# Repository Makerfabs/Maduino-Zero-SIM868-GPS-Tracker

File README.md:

# Maduino-Zero-SIM868-GPS-Tracker
Maduino Zero SIM868 GPS Tracker

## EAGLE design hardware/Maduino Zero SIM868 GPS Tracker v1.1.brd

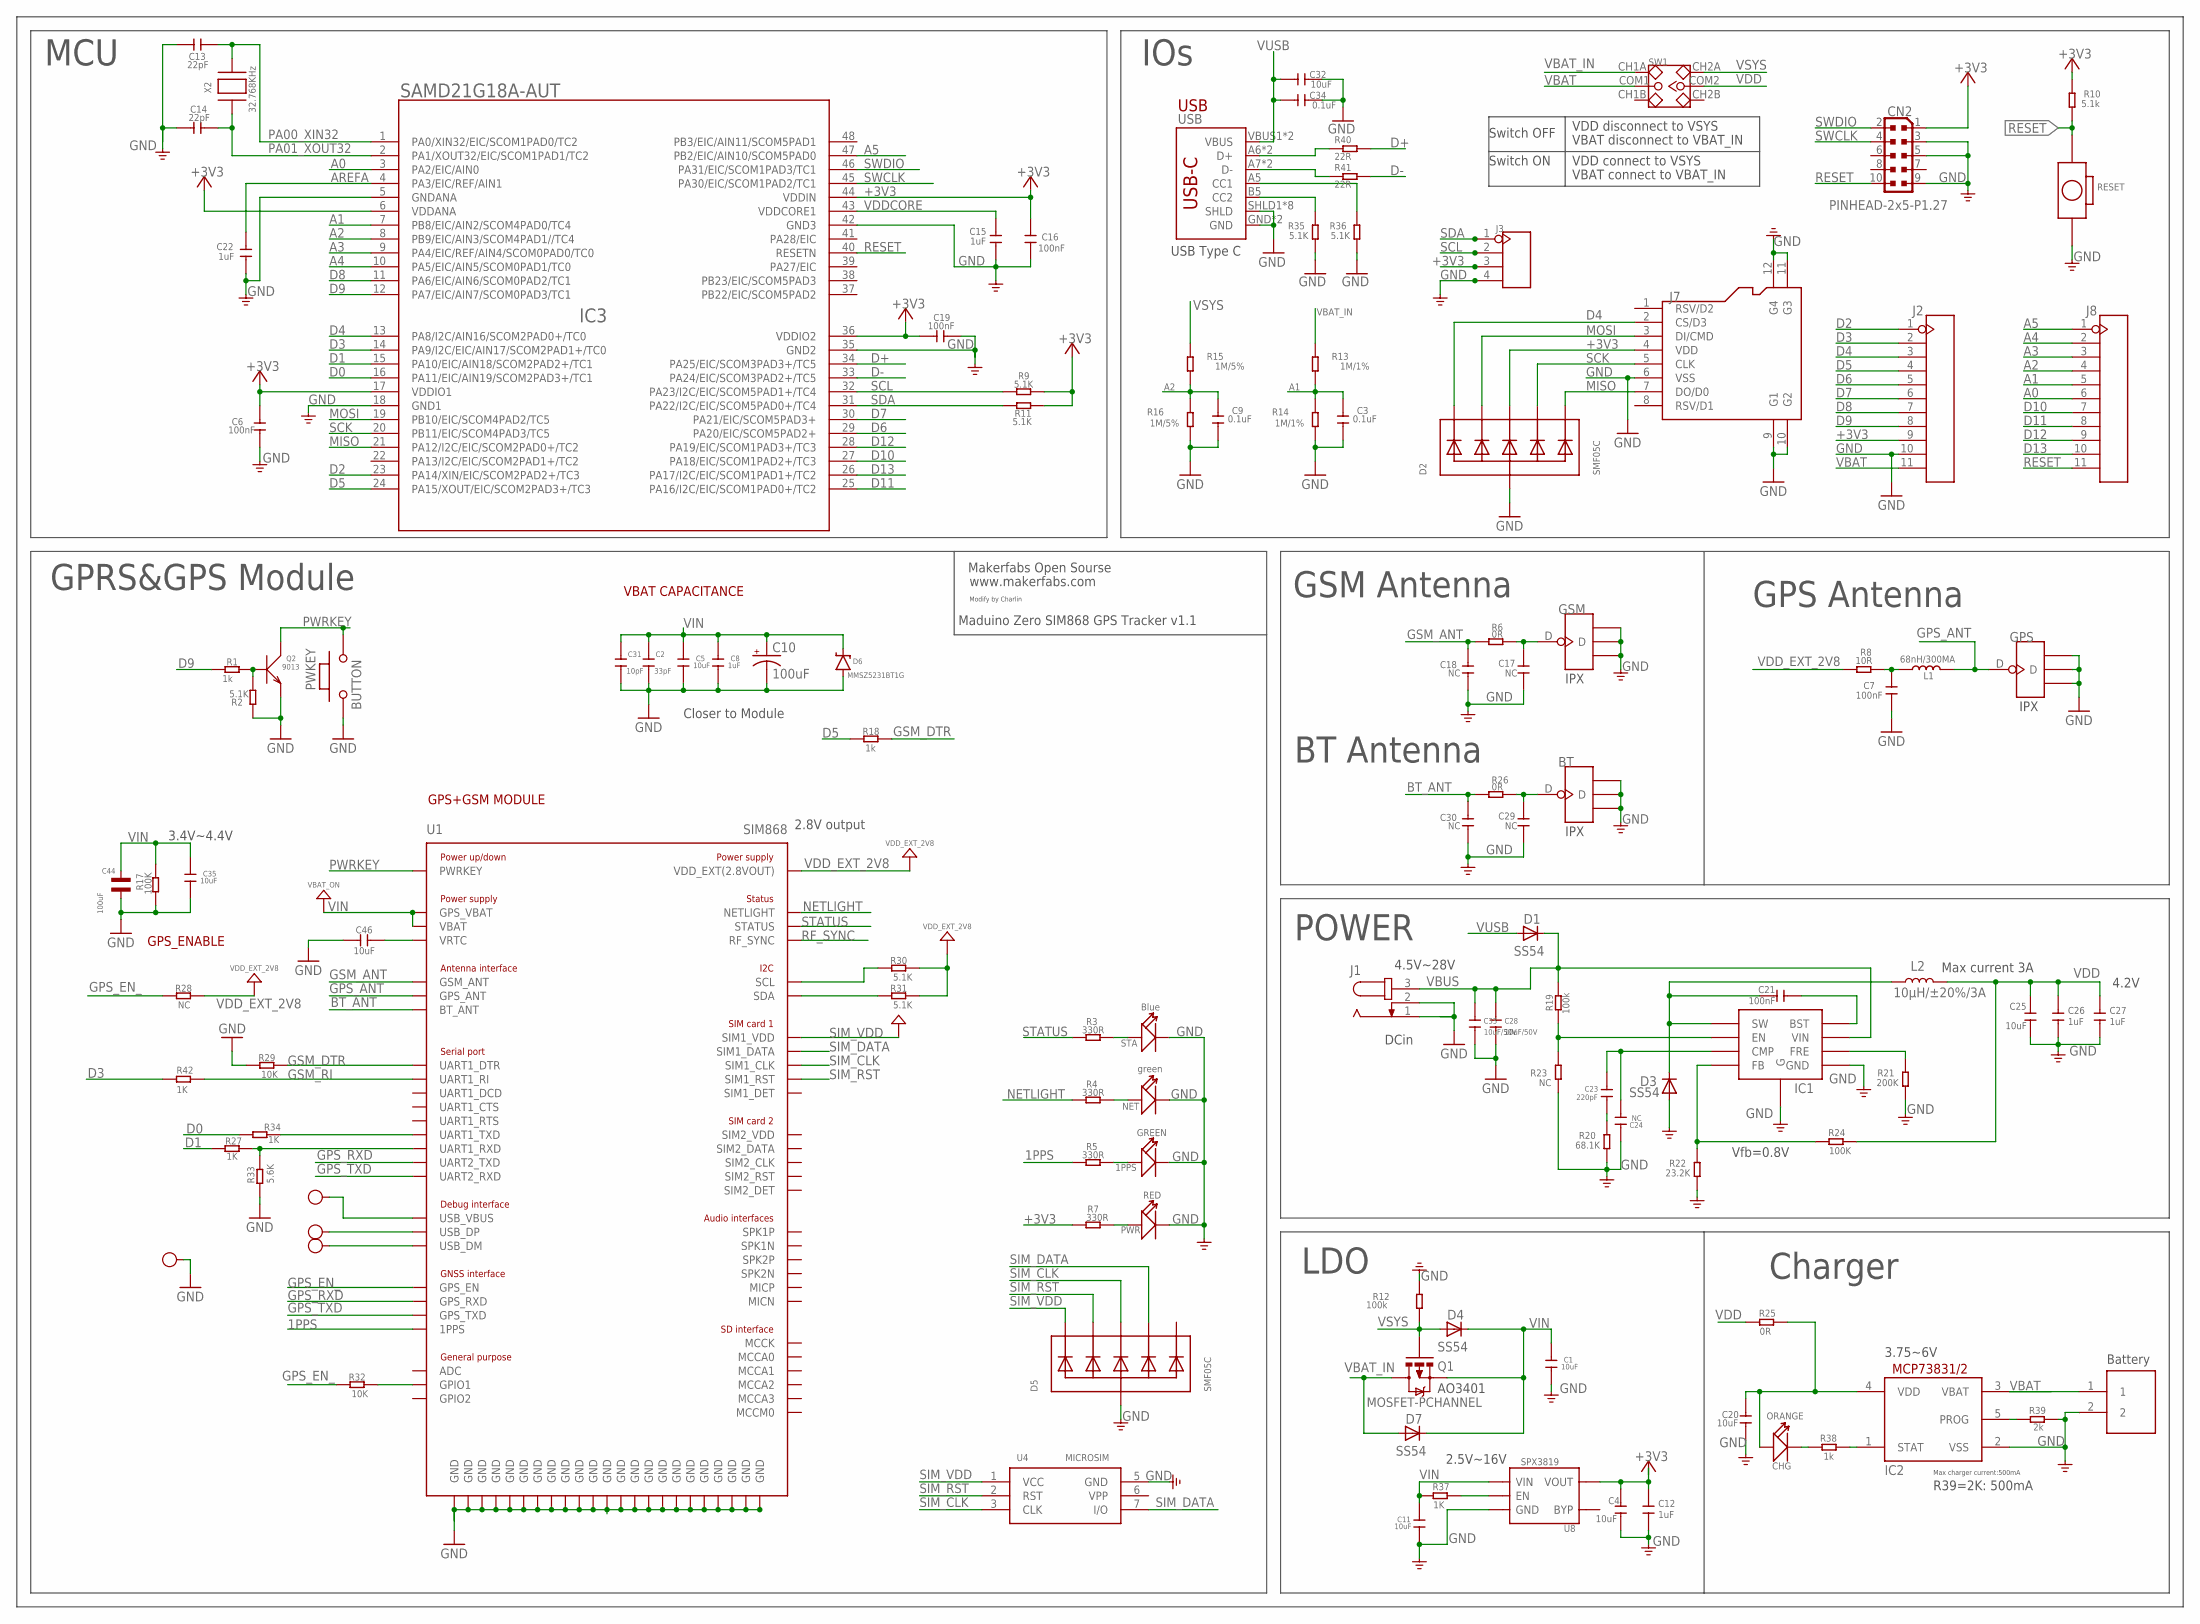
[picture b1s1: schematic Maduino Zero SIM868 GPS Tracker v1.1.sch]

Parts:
1PPS: GREEN; LED-0603
BT: ANTENNA-U-FL; 4P-U-FL
C1, C4, C5, C11, C20, C25, C32, C35: 10uF; 0603
C2: 33pF; 0603
C3, C9, C34: 0.1uF; 0603
C6, C7, C16, C19, C21: 100nF; 0603
C8, C12, C15, C22, C26, C27: 1uF; 0603
C10: 100uF; EIA3528
C13, C14: 22pF; 0603
C17, C18, C29, C30: NC; 0402
C23: 220pF; 0603
C24: NC; 0603
C28, C33: 10uF/50V; 0603
C31: 10pF; 0603
C44: 100uF; C1206; MPN CL31A107MQHNNNE
C46: 10uF; 0805
CHG: ORANGE; D0603
CN2: PINHEAD-2x5-P1.27; PINHEAD_2X05_127
D1, D3, D4, D7: SS54; DO-214AC
D2, D5: SMF05C; SOT363
D6: MMSZ5231BT1G; SOD-123
DN: TEST-POINT'4545'; TP-D45MIL; PARTNO DNP
DP: TEST-POINT'4545'; TP-D45MIL; PARTNO DNP
GND20: TEST-POINT'4545'; TP-D45MIL; PARTNO DNP
GPS: ANTENNA-U-FL; 4P-U-FL
GSM: ANTENNA-U-FL; 4P-U-FL
IC1: MP1584; SOIC8E
IC2: MCP73831/OT; SOT23-5L
IC3: SAMD21G18A-AUT; TQFP48-7X7
J1: JACK-PLUG1; SPC4078
J2, J8: HEADER-11P-2.54; 11P-2.54
J3: HEADER-4P-60/35MILROUND; 4P-65/35ROUND
J6: PH2.0-2P-90-DIP
J7: HOLDER-MICROSD-8P; 8P-SMD
L1: 68nH/300MA; L0603
L2: 10µH/±20%/3A; SRN6045
NET: green; LED-0603
PWKEY: BUTTON; 157SW
PWR: RED; LED-0603
Q1: MOSFET-PCHANNEL; SOT23-3
Q2: 9013; SOT23
R1, R18, R38: 1k; R0603
R2, R9, R11, R30, R31, R35, R36: 5.1K; R0603
R3, R4, R5, R7: 330R; R0603
R6, R25, R26: 0R; R0603
R8: 10R; R0603
R10: 5.1k; R0603
R12, R19: 100k; R0603
R13, R14: 1M/1%; R0603
R15, R16: 1M/5%; R0603
R17, R24: 100K; R0603
R20: 68.1K; R0603
R21: 200K; R0603
R22: 23.2K; R0603
R23, R28: NC; R0603
R27, R34, R37, R42: 1K; R0603
R29, R32: 10K; R0603
R33: 5.6K; R0603
R39: 2k; R0603
R40, R41: 22R; R0603
RESET: BOTTON-2P-90D; 2P-7.62X3.56-90D
STA: Blue; LED-0603
SW1: SWITCH-2CH-6P; 6P-2CH-2.54-7.6X3.0
U1: SIM868; MPN SIM868
U4: MICROSIM
U8: SPX3819; SOT23-5
USB: USB_C5; USB-C-16P-5
VUSB: TEST-POINT'4545'; TP-D45MIL; PARTNO DNP
X2: 32.768KHz; XTAL3215

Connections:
1PPS: R5.1, U1.60_ (1PPS)
+3V3: C4.2, C6.2, C12.2, C16.1, C19.1, CN2.1, D2.4 (C3), IC3.6 (VDDANA), IC3.17 (VDDIO1), IC3.36 (VDDIO2), IC3.44 (VDDIN), J2.9, J3.3, J7.4 (VDD), R7.1, R9.2, R10.2, R11.2, U8.5 (VOUT)
A0: IC3.3 (PA2/EIC/AIN0), J8.6
A1: C3.1, IC3.7 (PB8/EIC/AIN2/SCOM4PAD0/TC4), J8.5, R13.1, R14.2
A2: C9.1, IC3.8 (PB9/EIC/AIN3/SCOM4PAD1//TC4), J8.4, R15.1, R16.2
A3: IC3.9 (PA4/EIC/REF/AIN4/SCOM0PAD0/TC0), J8.3
A4: IC3.10 (PA5/EIC/AIN5/SCOM0PAD1/TC0), J8.2
A5: IC3.47 (PB2/EIC/AIN10/SCOM5PAD0), J8.1
AREFA: C22.1, IC3.4 (PA3/EIC/REF/AIN1)
BT_ANT: C30.2, R26.1, U1.20_ (BT_ANT)
D0: IC3.16 (PA11/EIC/AIN19/SCOM2PAD3+/TC1), R34.1
D1: IC3.15 (PA10/EIC/AIN18/SCOM2PAD2+/TC1), R27.1
D2: IC3.23 (PA14/XIN/EIC/SCOM2PAD2+/TC3), J2.1
D3: IC3.14 (PA9/I2C/EIC/AIN17/SCOM2PAD1+/TC0), J2.2, R42.1
D4: D2.1 (C1), IC3.13 (PA8/I2C/AIN16/SCOM2PAD0+/TC0), J2.3, J7.2 (CS/D3)
D5: IC3.24 (PA15/XOUT/EIC/SCOM2PAD3+/TC3), J2.4, R18.1
D6: IC3.29 (PA20/EIC/SCOM5PAD2+), J2.5
D7: IC3.30 (PA21/EIC/SCOM5PAD3+), J2.6
D8: IC3.11 (PA6/EIC/AIN6/SCOM0PAD2/TC1), J2.7
D9: IC3.12 (PA7/EIC/AIN7/SCOM0PAD3/TC1), J2.8, R1.1
D10: IC3.27 (PA18/EIC/SCOM1PAD2+/TC3), J8.7
D11: IC3.25 (PA16/I2C/EIC/SCOM1PAD0+/TC2), J8.8
D12: IC3.28 (PA19/EIC/SCOM1PAD3+/TC3), J8.9
D13: IC3.26 (PA17/I2C/EIC/SCOM1PAD1+/TC2), J8.10
D+: IC3.34 (PA25/EIC/SCOM3PAD3+/TC5), R40.1
D-: IC3.33 (PA24/EIC/SCOM3PAD2+/TC5), R41.1
GND: 1PPS.-, BT.GND1, BT.GND2, BT.GND3, C1.1, C2.1, C3.2, C4.1, C5.1, C6.1, C7.1, C8.1, C9.2, C10.C (-), C11.1, C12.1, C13.2, C14.2, C15.2, C16.2, C17.1, C18.1, C19.2, C20.1, C22.2, C24.2, C25.1, C26.1, C27.1, C28.2, C29.1, C30.1, C31.1, C32.2, C33.2, C34.2, C35.1, C44.P$2, C46.2, CN2.3, CN2.5, CN2.9, D2.2 (A), D3.A, D5.2 (A), D6.A, GND20.T, GPS.GND1, GPS.GND2, GPS.GND3, GSM.GND1, GSM.GND2, GSM.GND3, IC1.P$5 (GND), IC1.P$9 (G), IC2.2 (VSS), IC3.5 (GNDANA), IC3.18 (GND1), IC3.35 (GND2), IC3.42 (GND3), J1.1, J1.2, J2.10, J3.4, J6.2, J7.6 (VSS), J7.9 (G1), J7.10 (G2), J7.11 (G3), J7.12 (G4), NET.-, PWKEY.1, PWR.-, Q2.2 (E), R2.2, R12.2, R14.1, R16.1, R17.1, R20.1, R21.1, R22.1, R23.1, R29.1, R33.1, R35.1, R36.1, R39.2, RESET.P$2 (2), STA.-, U1.8_ (GND), U1.13_ (GND), U1.19_ (GND), U1.21_ (GND), U1.27_ (GND), U1.30_ (GND), U1.31_ (GND), U1.33_ (GND), U1.36_ (GND), U1.37_ (GND), U1.45_ (GND), U1.63_ (GND), U1.66_ (GND), U1.67_ (GND), U1.69_ (GND), U1.70_ (GND), U1.71_ (GND), U1.72_ (GND), U1.73_ (GND), U1.74_ (GND), U1.75_ (GND), U1.76_ (GND), U1.77_ (GND), U4.5 (GND), U8.2 (GND), USB.GND, USB.GND2 (GND), USB.SHLD1 (SHLD), USB.SHLD2 (SHLD), USB.SHLD3 (SHLD), USB.SHLD4 (SHLD), USB.SHLD5 (SHLD), USB.SHLD6 (SHLD), USB.SHLD7 (SHLD), USB.SHLD8 (SHLD)
GPS_ANT: GPS.D, L1.2, U1.68_ (GPS_ANT)
GPS_EN_: R28.1, R32.1, U1.59_ (GPS_EN)
GPS_RXD: U1.22_ (UART2_TXD), U1.62_ (GPS_RXD)
GPS_TXD: U1.23_ (UART2_RXD), U1.61_ (GPS_TXD)
GSM_ANT: C18.2, R6.1, U1.32_ (GSM_ANT)
GSM_DTR: R18.2, R29.2, U1.6_ (UART1_DTR)
GSM_RI: R42.2, U1.7_ (UART1_RI)
MISO: D2.6 (C5), IC3.21 (PA12/I2C/EIC/SCOM2PAD0+/TC2), J7.7 (DO/D0)
MOSI: D2.3 (C2), IC3.19 (PB10/EIC/SCOM4PAD2/TC5), J7.3 (DI/CMD)
unnamed: NET.+, R4.2
unnamed: 1PPS.+, R5.2
unnamed: PWR.+, R7.2
unnamed: R31.1, U1.64_ (SDA)
unnamed: C21.1, D3.C, IC1.P$1 (SW), L2.1
unnamed: C21.2, IC1.P$8 (BST)
unnamed: R3.2, STA.+
unnamed: C20.2, CHG.+, IC2.4 (VDD), R25.2
unnamed: IC1.P$4 (FB), R22.2, R24.1
unnamed: C23.2, C24.1, IC1.P$3 (CMP)
unnamed: C23.1, R20.2
unnamed: BT.D, C29.2, R26.2
unnamed: IC1.P$6 (FRE), R21.2
unnamed: IC1.P$2 (EN), R19.1, R23.2
unnamed: R30.1, U1.65_ (SCL)
unnamed: R27.2, R33.2, U1.2_ (UART1_RXD)
unnamed: R34.2, U1.1_ (UART1_TXD)
unnamed: R32.2, U1.57_ (GPIO1)
unnamed: U1.24_ (USB_VBUS), VUSB.T
unnamed: C7.2, L1.1, R8.2
unnamed: DP.T, U1.25_ (USB_DP)
unnamed: DN.T, U1.26_ (USB_DM)
unnamed: R37.2, U8.3 (EN)
unnamed: CHG.-, R38.1
unnamed: IC2.1 (STAT), R38.2
unnamed: R36.2, USB.A5 (CC1)
unnamed: R35.2, USB.B5 (CC2)
unnamed: C46.1, U1.28_ (VRTC)
unnamed: IC2.5 (PROG), R39.1
unnamed: R40.2, USB.A6 (D+), USB.B6 (D+)
unnamed: R41.2, USB.A7 (D-), USB.B7 (D-)
unnamed: Q2.1 (B), R1.2, R2.1
unnamed: C17.2, GSM.D, R6.2
NETLIGHT: R4.1, U1.41_ (NETLIGHT)
P$1: R30.2, R31.2
PA00_XIN32: C13.1, IC3.1 (PA0/XIN32/EIC/SCOM1PAD0/TC2), X2.P$2
PA01_XOUT32: C14.1, IC3.2 (PA1/XOUT32/EIC/SCOM1PAD1/TC2), X2.P$1
PWRKEY: PWKEY.2, Q2.3 (C), U1.39_ (PWRKEY)
RESET: CN2.10, IC3.40 (RESETN), J8.11, R10.1, RESET.P$1 (1)
RF_SYNC: U1.29_ (RF_SYNC)
SCK: D2.5 (C4), IC3.20 (PB11/EIC/SCOM4PAD3/TC5), J7.5 (CLK)
SCL: IC3.32 (PA23/I2C/EIC/SCOM5PAD1+/TC4), J3.2, R9.1
SDA: IC3.31 (PA22/I2C/EIC/SCOM5PAD0+/TC4), J3.1, R11.1
SIM2_VDD: U1.56_ (SIM2_VDD)
SIM_CLK: D5.4 (C3), U1.16_ (SIM1_CLK), U4.3 (CLK)
SIM_DATA: D5.5 (C4), U1.15_ (SIM1_DATA), U4.7 (I/O)
SIM_RST: D5.3 (C2), U1.17_ (SIM1_RST), U4.2 (RST)
SIM_VDD: D5.1 (C1), U1.18_ (SIM1_VDD), U4.1 (VCC)
STATUS: R3.1, U1.42_ (STATUS)
SWCLK: CN2.4, IC3.45 (PA30/EIC/SCOM1PAD2/TC1)
SWDIO: CN2.2, IC3.46 (PA31/EIC/SCOM1PAD3/TC1)
VBAT: IC2.3 (VBAT), J2.11, J6.1, SW1.COM1
VBAT_IN: D7.A, Q1.3 (D), R13.2, SW1.CH1A
VBUS: C28.1, C33.1, D1.C, IC1.P$7 (VIN), J1.3, R19.2
VDD: C25.2, C26.2, C27.2, L2.2, R24.2, R25.1, SW1.COM2
VDDCORE: C15.1, IC3.43 (VDDCORE1)
VDD_EXT_2V8: R8.1, R28.2, U1.40_ (VDD_EXT(2.8VOUT))
VIN: C1.2, C2.2, C5.2, C8.2, C10.A (+), C11.2, C31.2, C35.2, C44.P$1, D4.C, D6.C, D7.C, Q1.2 (S), R17.2, R37.1, U1.34_ (GPS_VBAT), U1.35_ (VBAT), U8.1 (VIN)
VSYS: D4.A, Q1.1 (G), R12.1, R15.2, SW1.CH2A
VUSB: C32.1, C34.1, D1.A, USB.VBUS1 (VBUS), USB.VBUS2 (VBUS)

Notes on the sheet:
GPS Antenna
GSM Antenna
GPRS&GPS Module
LDO
Max charger current:500mA
Charger
Makerfabs Open Sourse
www.makerfabs.com
Modify by Charlin
Maduino Zero SIM868 GPS Tracker v1.1
IOs
MCU
IPX
Battery
AO3401
Closer to Module
Switch OFF
Switch ON
VDD disconnect to VSYS
VBAT disconnect to VBAT_IN
VDD connect to VSYS
VBAT connect to VBAT_IN
4.2V
Max current 3A
DCin
4.5V~28V
R39=2K: 500mA
3.75~6V
Vfb=0.8V
2.5V~16V
GPS+GSM MODULE
GPS_ENABLE
VBAT CAPACITANCE
3.4V~4.4V
2.8V output
USB
USB Type C
BT Antenna
POWER

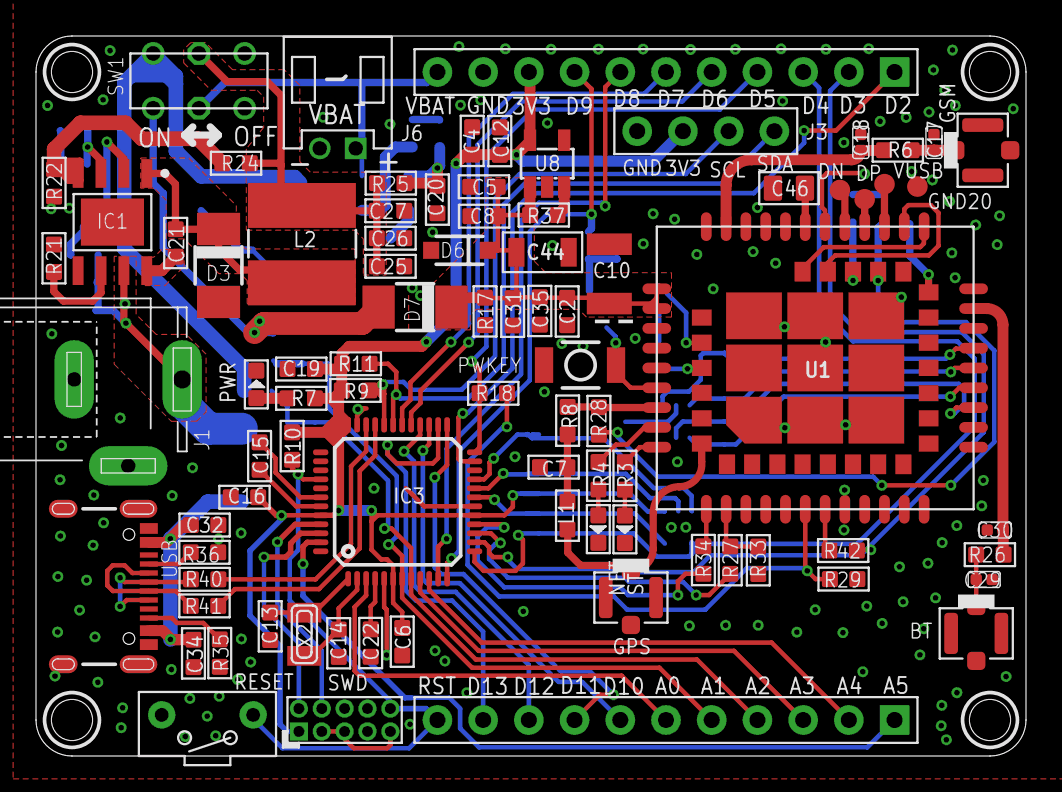
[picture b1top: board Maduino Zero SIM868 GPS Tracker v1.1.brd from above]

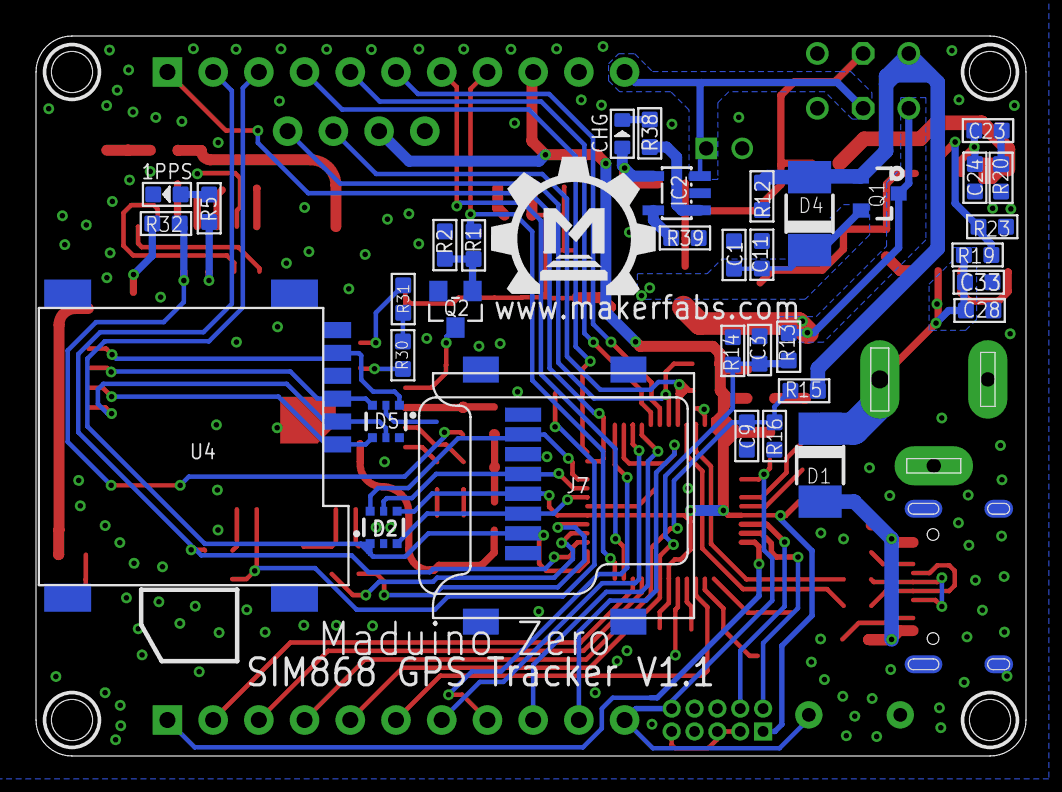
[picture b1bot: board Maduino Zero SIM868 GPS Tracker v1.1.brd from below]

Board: 2 copper layers, 55.0 x 40.0 mm, 121 parts (36 on the bottom side), 94 nets.

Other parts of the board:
U$1: MAKERFABS_0.3

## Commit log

2023-10-07 Add hardware and example
2023-10-08 Add Spec of SIM868

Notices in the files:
parts and their libraries:
microbuilder: This work is placed in the public domain, and may be freely used for commercial and non-commercial work with the following conditions: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
User-Submitted: Licensing: Creative Commons ShareAlike 4.0 International - https://creativecommons.org/licenses/by-sa/4.0
